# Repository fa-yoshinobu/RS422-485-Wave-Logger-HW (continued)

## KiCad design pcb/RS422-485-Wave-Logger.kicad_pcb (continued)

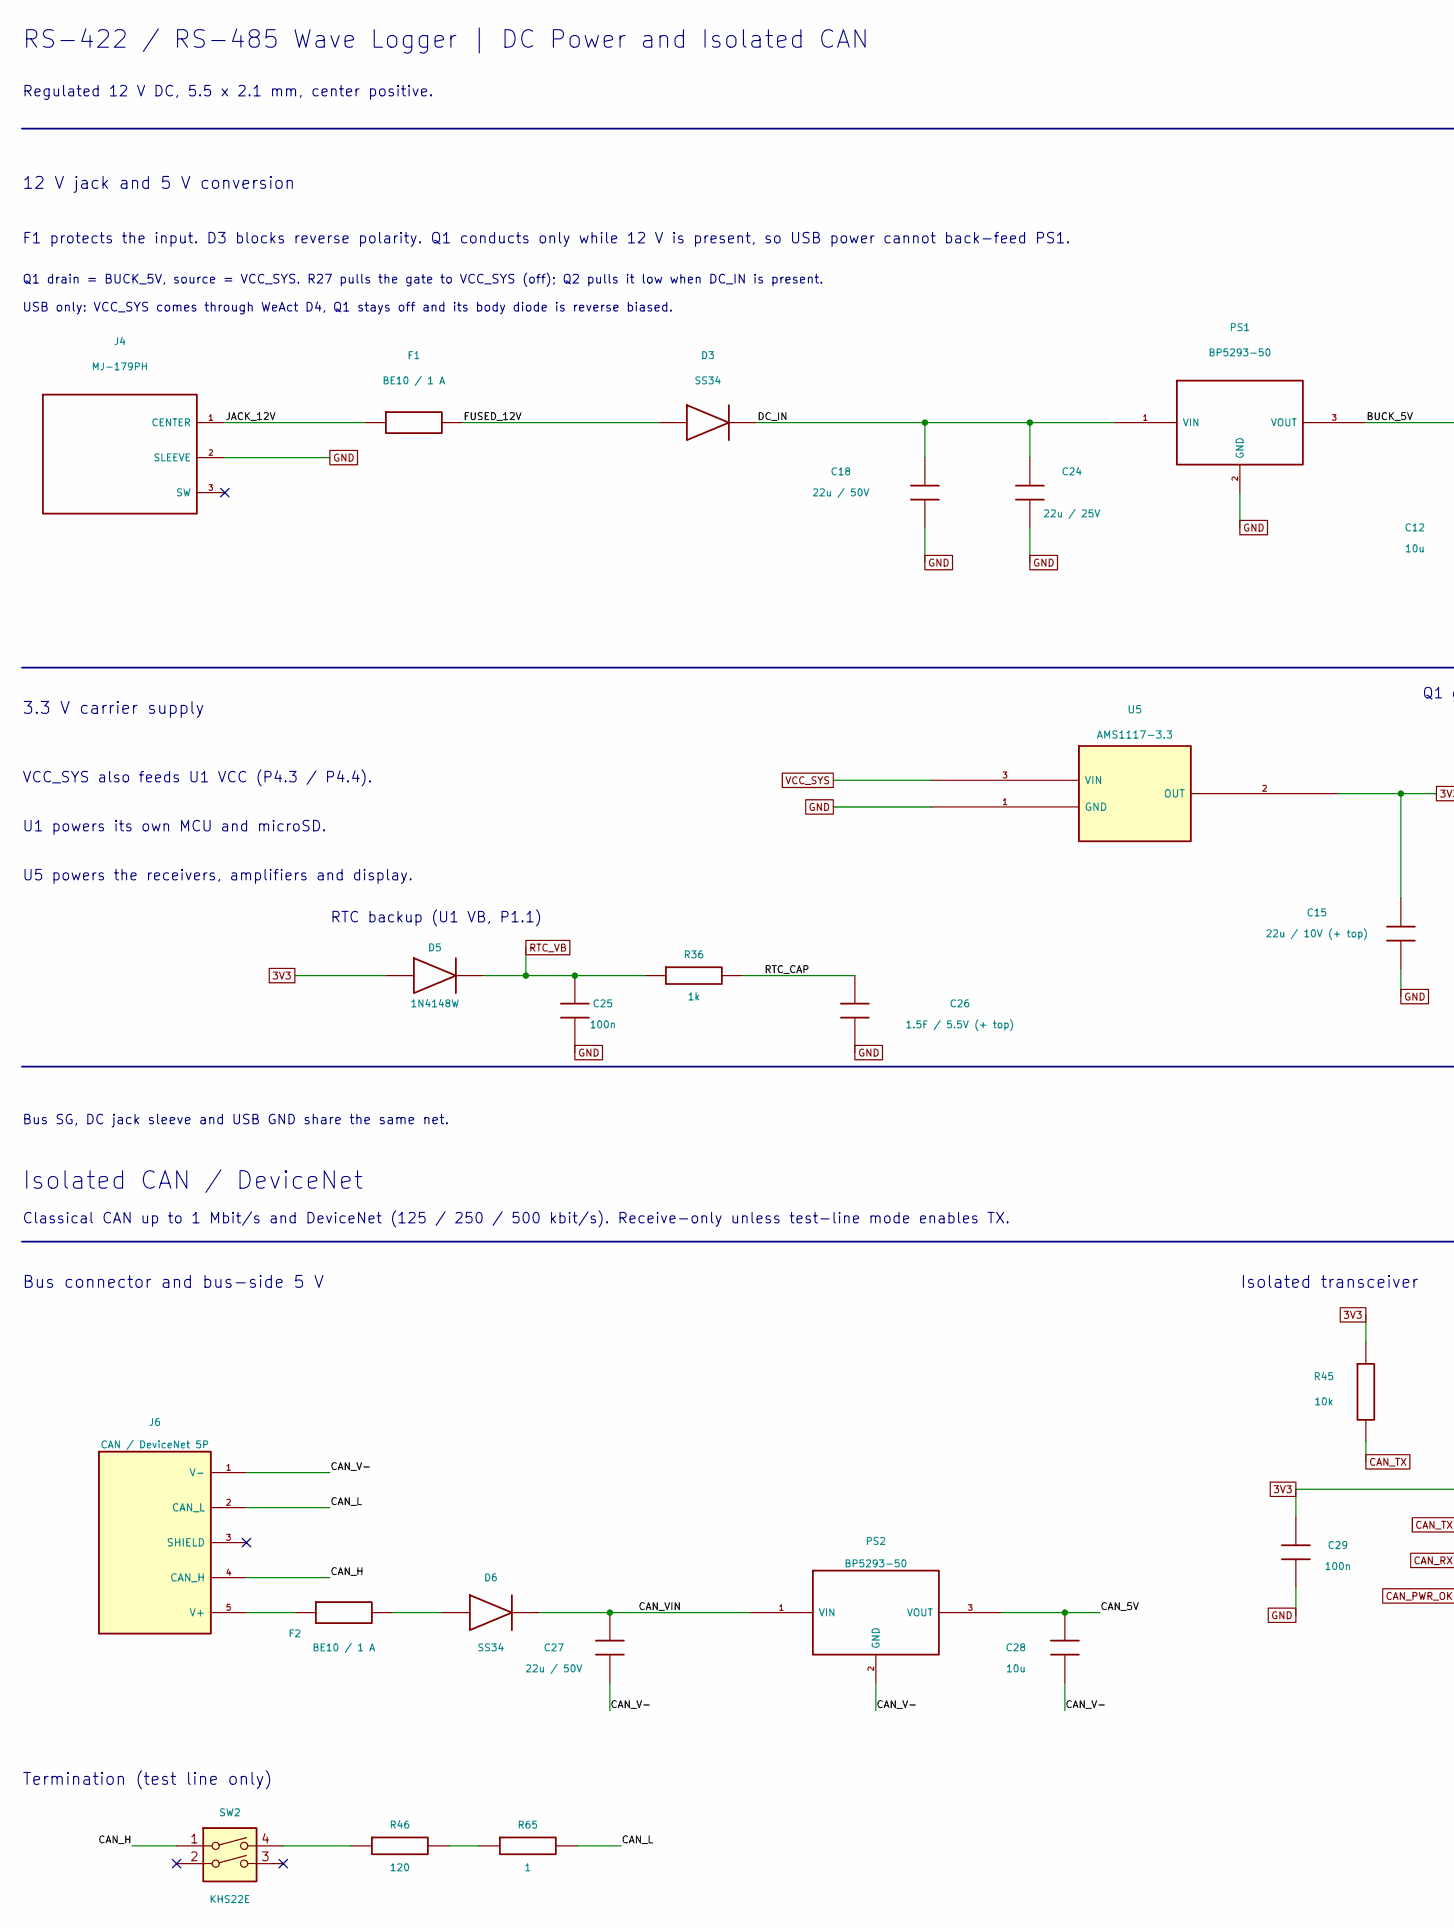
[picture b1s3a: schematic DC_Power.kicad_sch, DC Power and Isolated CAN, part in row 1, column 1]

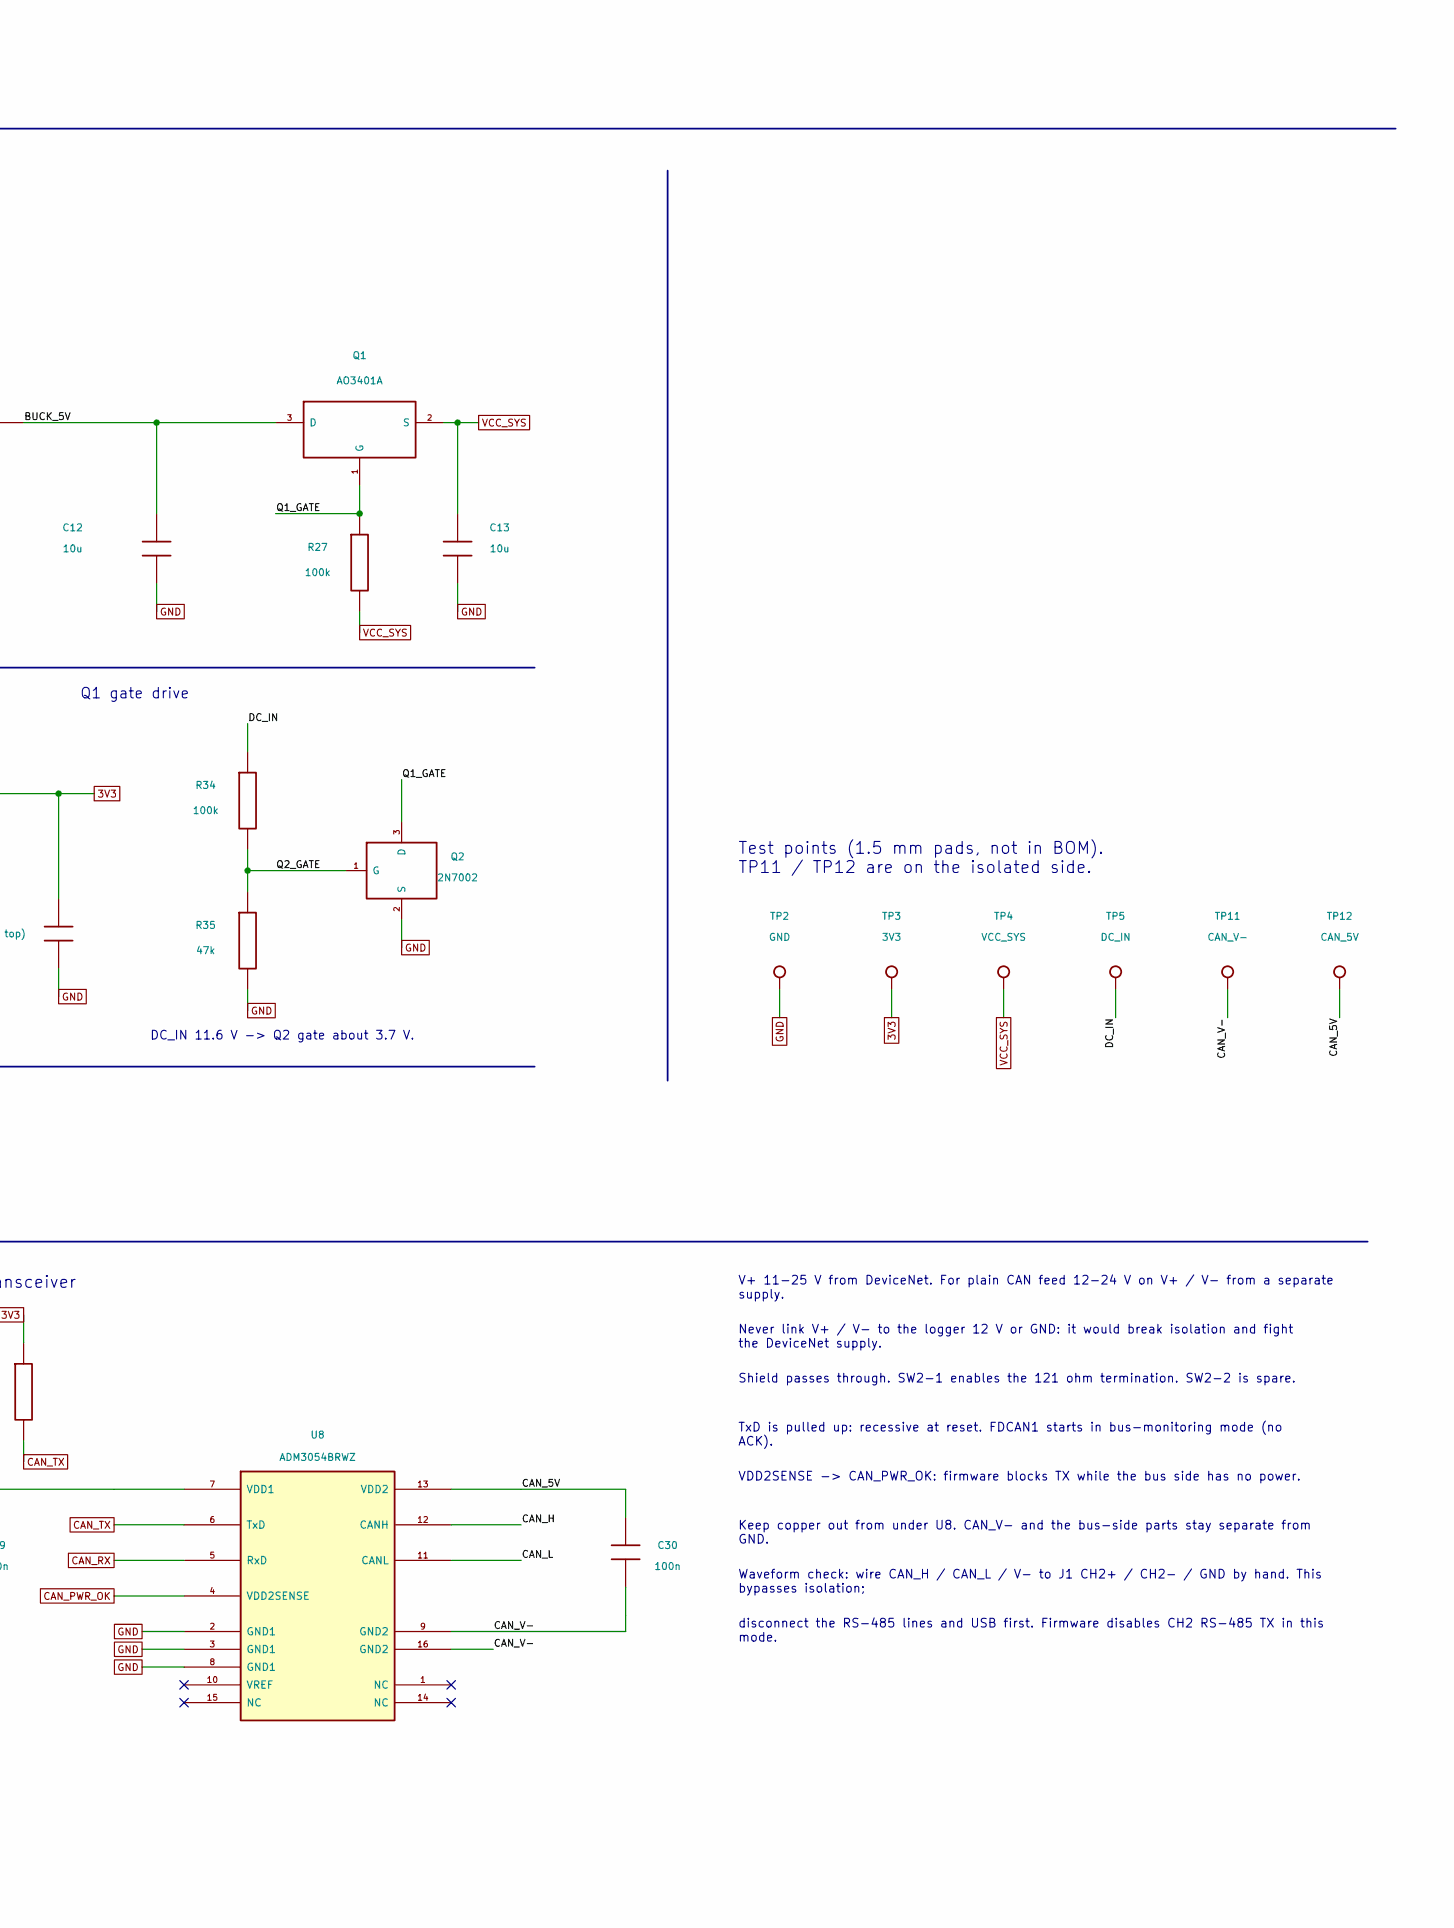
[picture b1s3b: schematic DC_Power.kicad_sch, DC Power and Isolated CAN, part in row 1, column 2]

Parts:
C12, C13, C28: 10u; C_0805_2012Metric
C15: 22u / 10V (+ top); CP_EIA-3528-21_Kemet-B
C18, C27: 22u / 50V; Murata_RDE_108156_Horizontal_P5mm
C24: 22u / 25V; C_1206_3216Metric
C25, C29, C30: 100n; C_0603_1608Metric
C26: 1.5F / 5.5V (+ top); KAMCAP_SE-5R5-D155VY_Horizontal
D3, D6: SS34; D_SMA
D5: 1N4148W; D_SOD-123
F1, F2: BE10 / 1 A; Daito_BE
J4: MJ-179PH; MJ179PH_BoardEdge
J6: CAN / DeviceNet 5P; Akizuki_APF142_APF143_5P_P5.08
PS1, PS2: BP5293-50; ROHM_BP5293_SIP3
Q1: AO3401A; SOT-23
Q2: 2N7002; SOT-23
R27, R34: 100k; R_0603_1608Metric
R35: 47k; R_0603_1608Metric
R36: 1k; R_0603_1608Metric
R45: 10k; R_0603_1608Metric
R46: 120; R_1206_3216Metric
R65: 1; R_0603_1608Metric
SW2: KHS22E; OTAX_KHS22E
TP2: GND; TestPoint_Pad_D1.5mm
TP3: 3V3; TestPoint_Pad_D1.5mm
TP4: VCC_SYS; TestPoint_Pad_D1.5mm
TP5: DC_IN; TestPoint_Pad_D1.5mm
TP11: CAN_V-; TestPoint_Pad_D1.5mm
TP12: CAN_5V; TestPoint_Pad_D1.5mm
U5: AMS1117-3.3; SOT-223-3_TabPin2
U8: ADM3054BRWZ; SOIC-16W_7.5x10.3mm_P1.27mm

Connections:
3V3: C15.1, C29.1, D5.2 (A), R45.1, TP3.1 (1_1), U5.2 (OUT), U8.7 (VDD1); also elsewhere on the board
/3 Power and CAN/BUCK_5V: C12.1, PS1.3 (VOUT), Q1.3 (D)
/3 Power and CAN/CAN_5V: C28.1, C30.1, PS2.3 (VOUT), TP12.1 (1_1), U8.13 (VDD2)
/3 Power and CAN/CAN_H: J6.4 (CAN_H), SW2.1, U8.12 (CANH)
/3 Power and CAN/CAN_L: J6.2 (CAN_L), R65.2, U8.11 (CANL)
/3 Power and CAN/CAN_V-: C27.2, C28.2, C30.2, J6.1 (V-), PS2.2 (GND), TP11.1 (1_1), U8.9 (GND2), U8.16 (GND2)
/3 Power and CAN/CAN_VIN: C27.1, D6.1 (K), PS2.1 (VIN)
/3 Power and CAN/DC_IN: C18.1, C24.1, D3.1 (K), PS1.1 (VIN), R34.1, TP5.1 (1_1)
/3 Power and CAN/FUSED_12V: D3.2 (A), F1.2
/3 Power and CAN/JACK_12V: F1.1, J4.1 (CENTER)
/3 Power and CAN/Q1_GATE: Q1.1 (G), Q2.3 (D), R27.1
/3 Power and CAN/Q2_GATE: Q2.1 (G), R34.2, R35.1
/3 Power and CAN/RTC_CAP: C26.1, R36.2
CAN_PWR_OK: U8.4 (VDD2SENSE); also elsewhere on the board
CAN_RX: U8.5 (RxD); also elsewhere on the board
CAN_TX: R45.2, U8.6 (TxD); also elsewhere on the board
GND: C12.2, C13.2, C15.2, C18.2, C24.2, C25.2, C26.2, C29.2, J4.2 (SLEEVE), PS1.2 (GND), Q2.2 (S), R35.2, TP2.1 (1_1), U5.1 (GND), U8.2 (GND1), U8.3 (GND1), U8.8 (GND1); also elsewhere on the board
unnamed: D6.2 (A), F2.2
unnamed: F2.1, J6.5 (V+)
unnamed: R46.1, SW2.4
unnamed: R46.2, R65.1
RTC_VB: C25.1, D5.1 (K), R36.1; also elsewhere on the board
VCC_SYS: C13.1, Q1.2 (S), R27.2, TP4.1 (1_1), U5.3 (VIN); also elsewhere on the board

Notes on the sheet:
RS-422 / RS-485 Wave Logger | DC Power and Isolated CAN
Regulated 12 V DC, 5.5 x 2.1 mm, center positive.
12 V jack and 5 V conversion
F1 protects the input. D3 blocks reverse polarity. Q1 conducts only while 12 V is present, so USB power cannot back-feed PS1.
3.3 V carrier supply
VCC_SYS also feeds U1 VCC (P4.3 / P4.4).
U1 powers its own MCU and microSD.
U5 powers the receivers, amplifiers and display.
Bus SG, DC jack sleeve and USB GND share the same net.
Q1 drain = BUCK_5V, source = VCC_SYS. R27 pulls the gate to VCC_SYS (off); Q2 pulls it low when DC_IN is present.
USB only: VCC_SYS comes through WeAct D4, Q1 stays off and its body diode is reverse biased.
Q1 gate drive
DC_IN 11.6 V -> Q2 gate about 3.7 V.
RTC backup (U1 VB, P1.1)
Isolated CAN / DeviceNet
Classical CAN up to 1 Mbit/s and DeviceNet (125 / 250 / 500 kbit/s). Receive-only unless test-line mode enables TX.
Bus connector and bus-side 5 V
V+ 11-25 V from DeviceNet. For plain CAN feed 12-24 V on V+ / V- from a separate supply.
Never link V+ / V- to the logger 12 V or GND: it would break isolation and fight the DeviceNet supply.
Shield passes through. SW2-1 enables the 121 ohm termination. SW2-2 is spare.
Termination (test line only)
Isolated transceiver
TxD is pulled up: recessive at reset. FDCAN1 starts in bus-monitoring mode (no ACK).
VDD2SENSE -> CAN_PWR_OK: firmware blocks TX while the bus side has no power.
Keep copper out from under U8. CAN_V- and the bus-side parts stay separate from GND.
Waveform check: wire CAN_H / CAN_L / V- to J1 CH2+ / CH2- / GND by hand. This bypasses isolation;
disconnect the RS-485 lines and USB first. Firmware disables CH2 RS-485 TX in this mode.
Test points (1.5 mm pads, not in BOM). TP11 / TP12 are on the isolated side.

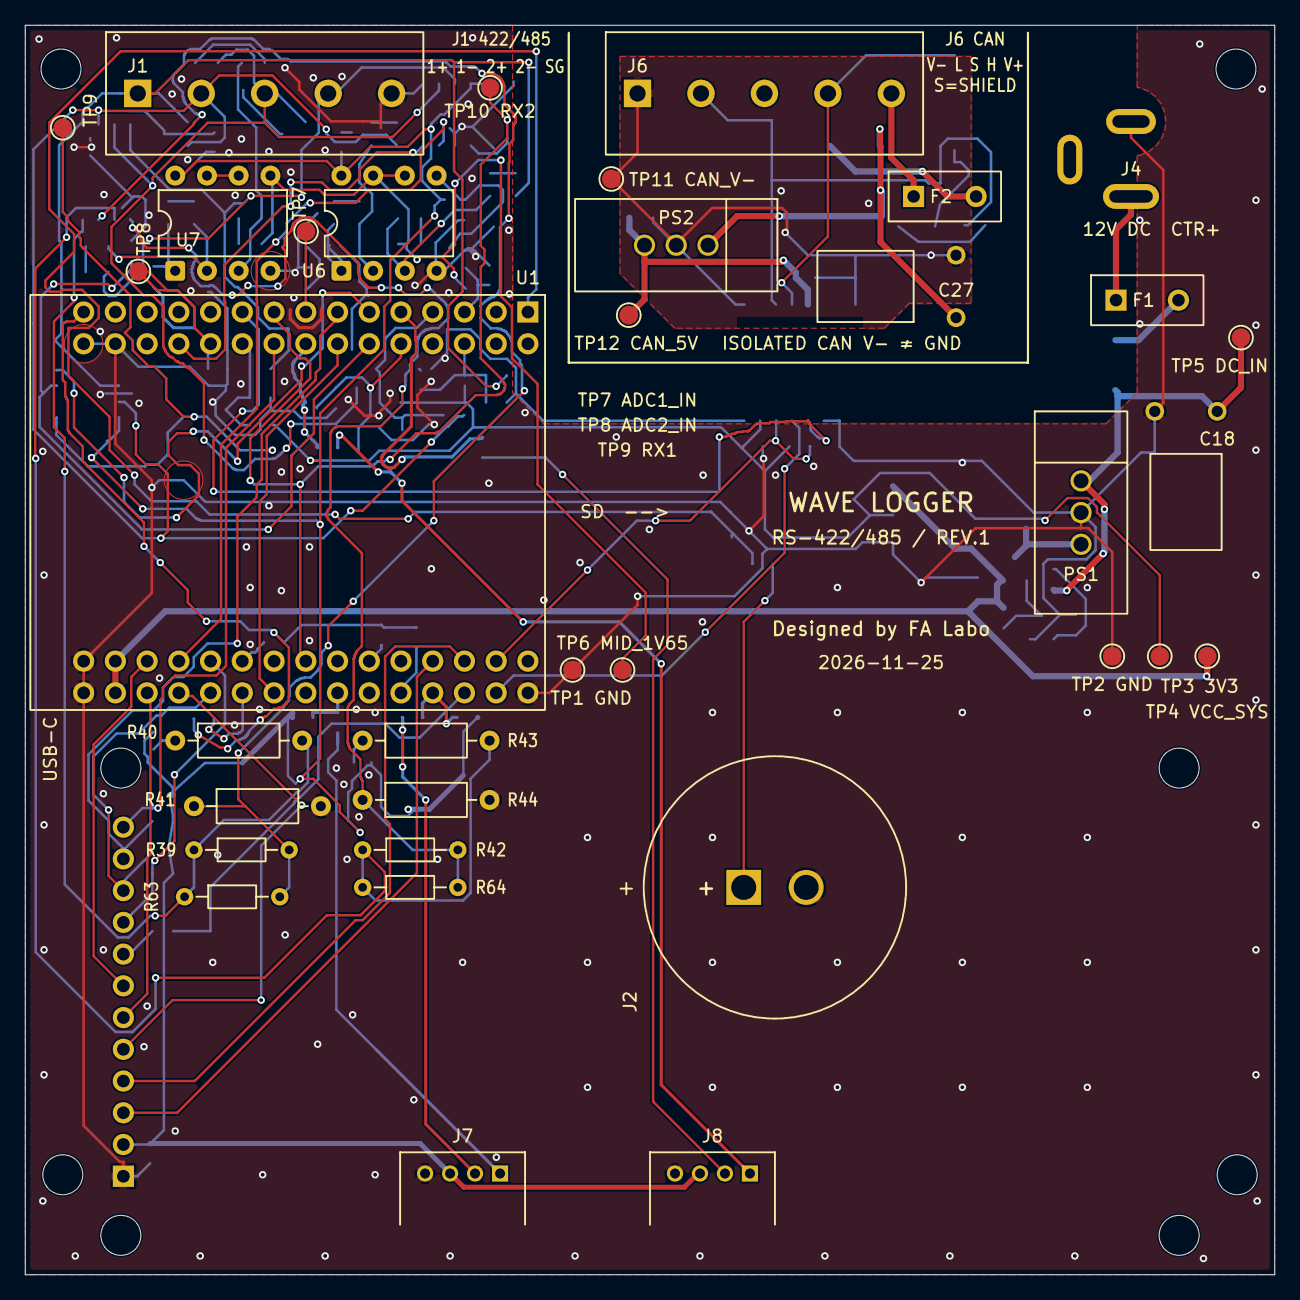
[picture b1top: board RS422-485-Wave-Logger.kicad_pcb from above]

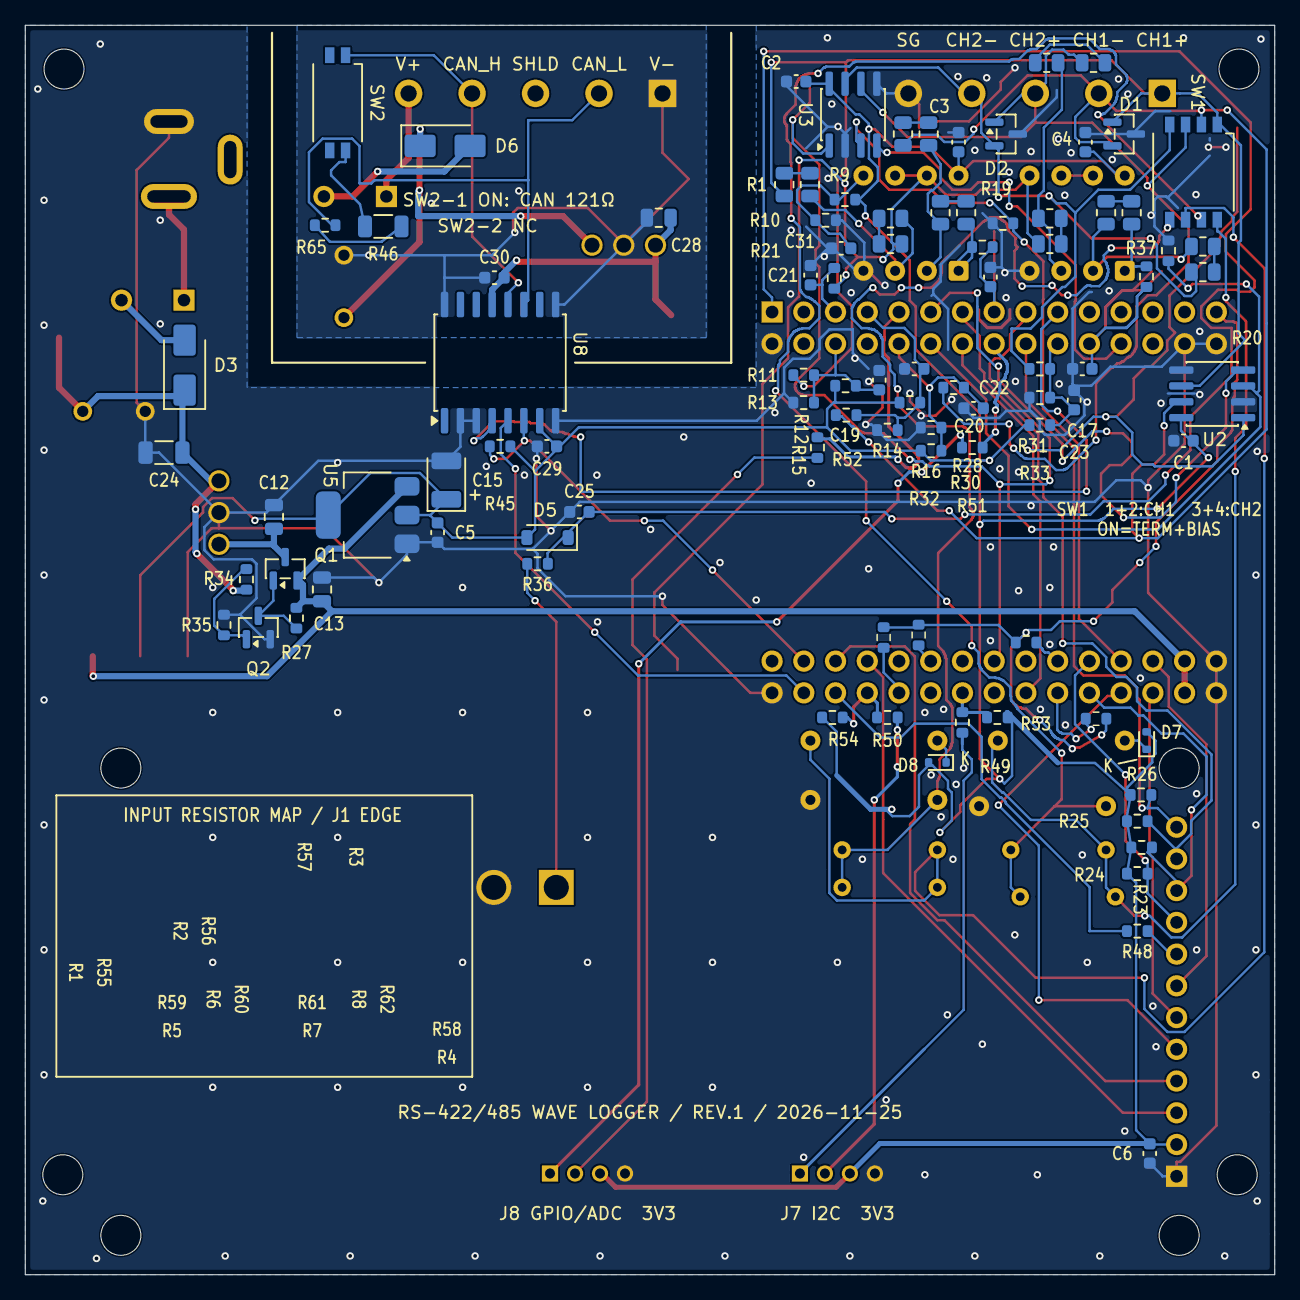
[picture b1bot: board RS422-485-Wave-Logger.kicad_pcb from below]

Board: 2 copper layers, 100.0 x 100.0 mm, 134 parts (94 on the bottom side), 87 nets.

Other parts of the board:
H1, H2, H3, H4: M3; M3_NPTH_3.2_Head5.5

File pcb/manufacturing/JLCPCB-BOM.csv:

"Comment","Designator","Footprint","JLCPCB Part #"
"SP3485EN-L/TR","U2,U3","SOIC-8_3.9x4.9mm_P1.27mm","C8963"
"AMS1117-3.3","U5","SOT-223-3_TabPin2","C6186"
"SS34","D3,D6","D_SMA","C8678"
"1N4148W","D5","D_SOD-123","C81598"
"AO3401A","Q1","SOT-23","C15127"
"2N7002","Q2","SOT-23","C8545"
"100k","R27,R34","R_0603_1608Metric","C25803"
"SM712","D1,D2","SOT-23","C502564"
"100n","C1,C2,C3,C4,C5,C6,C25,C29,C30,C31","C_0603_1608Metric","C14663"
"10u","C12,C13,C28","C_0805_2012Metric","C15850"
"22u / 25V","C24","C_1206_3216Metric","C12891"
"1n","C16,C17,C19,C20,C21,C22,C23","C_0603_1608Metric","C1588"
"200k","R11,R12,R28,R29","R_0603_1608Metric","C25811"
"47k","R13,R14,R15,R16,R30,R31,R32,R33,R35,R66,R67,R68,R69","R_0603_1608Metric","C25819"
"10k","R9,R10,R23,R24,R25,R26,R37,R38,R45","R_0603_1608Metric","C25804"
"330R","R19,R20,R21","R_0603_1608Metric","C23138"
"BAT54X","D7,D8","D_SOD-523","C19627026"
"120","R46","R_1206_3216Metric","C17909"
"1","R65","R_0603_1608Metric","C22936"
"10R","R48","R_0603_1608Metric","C22859"
"1k","R36","R_0603_1608Metric","C21190"
"100R","R49,R50,R51,R52","R_0603_1608Metric","C22775"
"4.7k","R53,R54","R_0603_1608Metric","C23162"
